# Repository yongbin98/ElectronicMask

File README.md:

# ElectronicMask
The code is for the assignment "Developing breathing-based vital signs detection models and control algorithms to improve sleep quality" <br>

# Sensors
`MCU` : STM32F765VI <br>
`Bluetooth` : E104-BT5005A <br>
`Pressure Sensor` : LPS22HHTR <br>
`Microphone` : SPH0645LM4H-1-8 <br>
`IMU Sensor` : LSM6DSMTR <br>
`PPG Sensor` : MAX86171 & SFH 7072 <br>
`EMG EOG EEG sensor` : ADS1299 <br>

# Developed ElectronicMask (Prototype)

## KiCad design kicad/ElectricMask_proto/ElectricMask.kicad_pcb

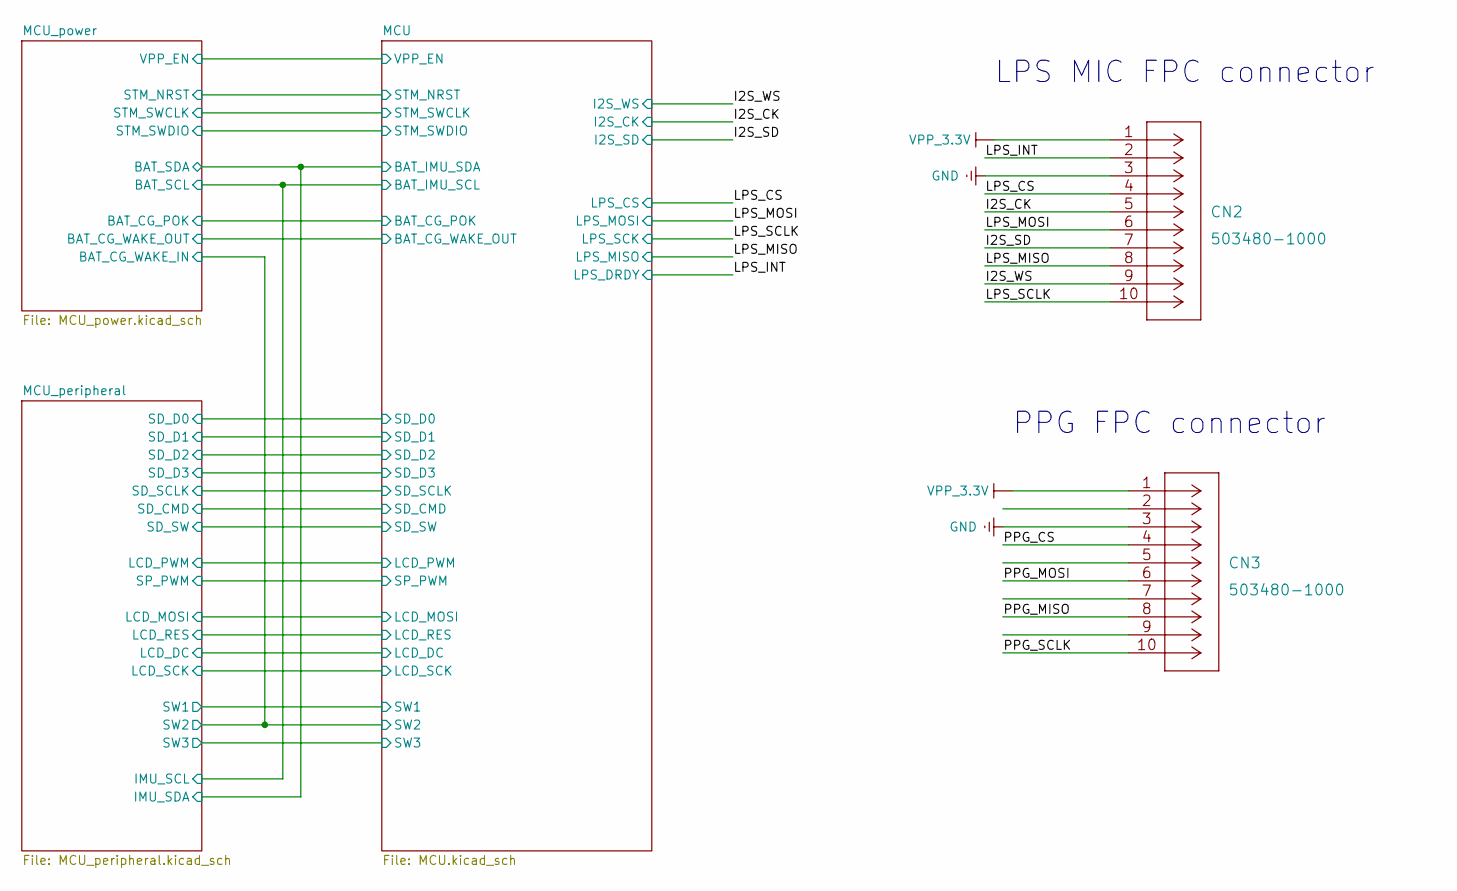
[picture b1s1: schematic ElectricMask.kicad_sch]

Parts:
CN2, CN3: 503480-1000

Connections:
/I2S_CK: CN2.5; also elsewhere on the board
/I2S_SD: CN2.7; also elsewhere on the board
/I2S_WS: CN2.9; also elsewhere on the board
/LPS_CS: CN2.4; also elsewhere on the board
/LPS_INT: CN2.2; also elsewhere on the board
/LPS_MISO: CN2.8; also elsewhere on the board
/LPS_MOSI: CN2.6; also elsewhere on the board
/LPS_SCLK: CN2.10; also elsewhere on the board

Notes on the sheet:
PPG FPC connector
LPS MIC FPC connector

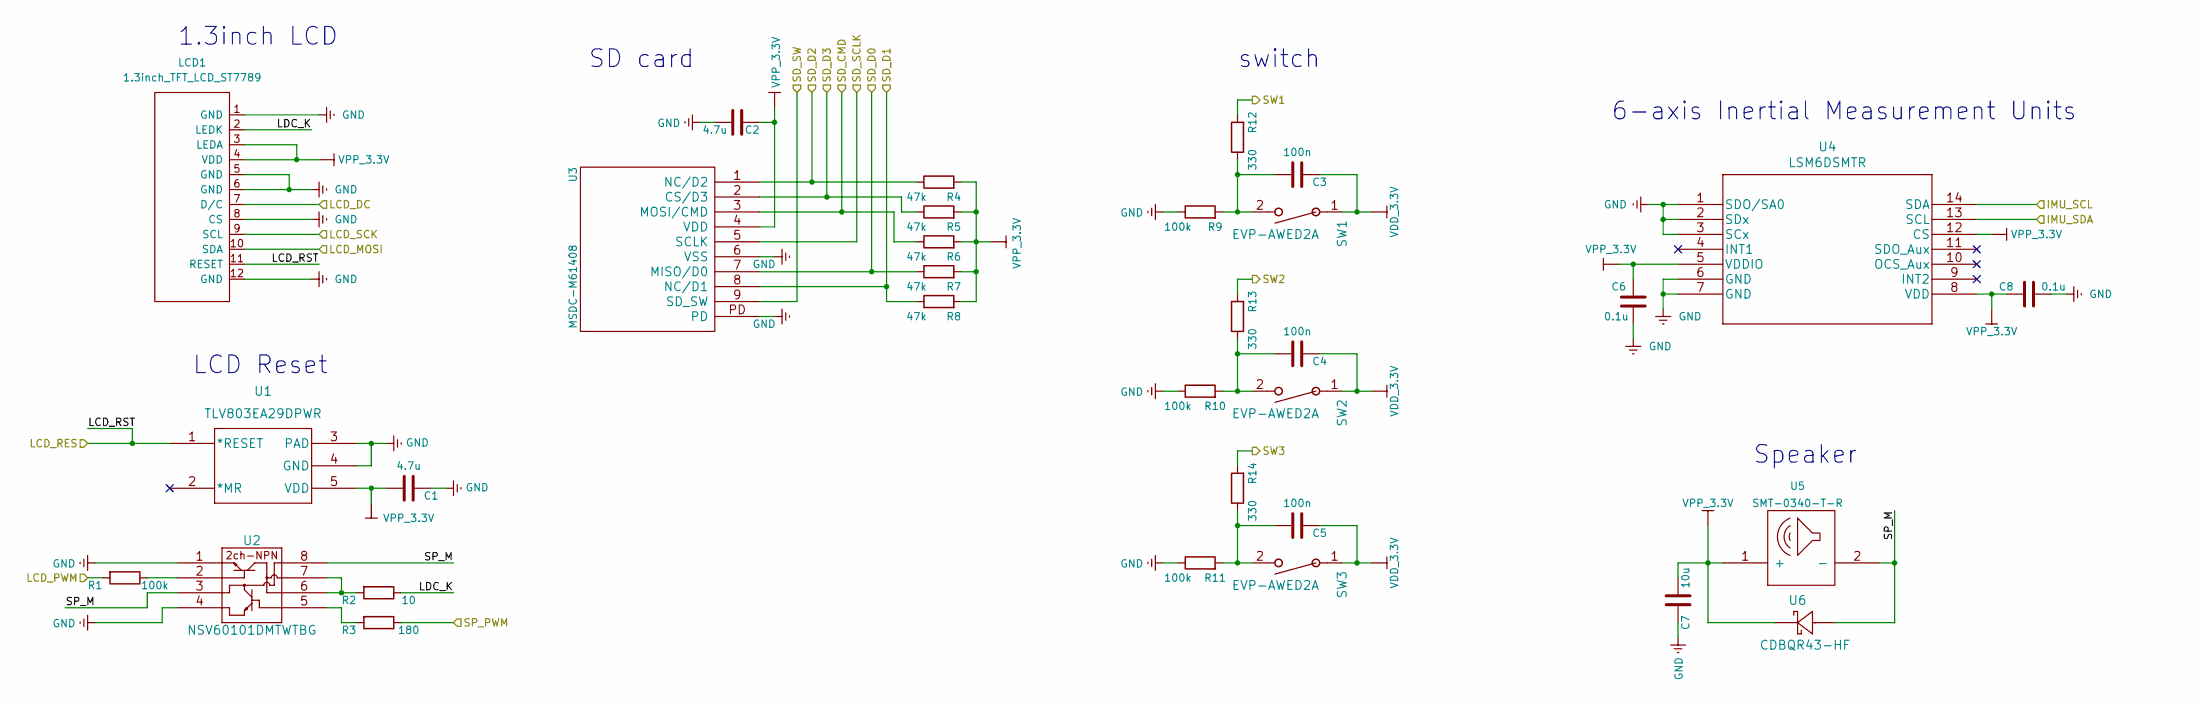
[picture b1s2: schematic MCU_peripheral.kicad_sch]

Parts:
C1, C2: 4.7u; UL_C_0402_1005Metric
C3, C4, C5: 100n; UL_C_0402_1005Metric
C6, C8: 0.1u; UL_C_0402_1005Metric
C7: 10u; UL_C_0402_1005Metric
LCD1: 1.3inch_TFT_LCD_ST7789
R1, R9, R10, R11: 100k; R_0402_1005Metric
R2: 10; R_0402_1005Metric
R3: 180; R_0402_1005Metric
R4, R5, R6, R7, R8: 47k; R_0402_1005Metric
R12, R13, R14: 330; R_0402_1005Metric
SW1, SW2, SW3: EVP-AWED2A
U1: TLV803EA29DPWR
U2: NSV60101DMTWTBG
U3: MSDC-M61408; MSDC-M61408(Micro_SD)
U4: LSM6DSMTR
U5: SMT-0340-T-R
U6: CDBQR43-HF

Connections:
/MCU/BAT_IMU_SCL: U4.14 (SDA); also elsewhere on the board
/MCU/BAT_IMU_SDA: U4.13 (SCL); also elsewhere on the board
/MCU/LCD_DC: LCD1.7 (D/C); also elsewhere on the board
/MCU/LCD_MOSI: LCD1.10 (SDA); also elsewhere on the board
/MCU/LCD_PWM: R1.2; also elsewhere on the board
/MCU/LCD_SCK: LCD1.9 (SCL); also elsewhere on the board
/MCU/SD_CMD: R6.1, U3.3 (MOSI/CMD); also elsewhere on the board
/MCU/SD_D0: R7.1, U3.7 (MISO/D0); also elsewhere on the board
/MCU/SD_D1: R8.1, U3.8 (NC/D1); also elsewhere on the board
/MCU/SD_D2: R4.1, U3.1 (NC/D2); also elsewhere on the board
/MCU/SD_D3: R5.1, U3.2 (CS/D3); also elsewhere on the board
/MCU/SD_SCLK: U3.5 (SCLK); also elsewhere on the board
/MCU/SD_SW: U3.9 (SD_SW); also elsewhere on the board
/MCU/SP_PWM: R3.1; also elsewhere on the board
/MCU/SW1: R12.2; also elsewhere on the board
/MCU/SW2: R13.2; also elsewhere on the board
/MCU/SW3: R14.2; also elsewhere on the board
/MCU_peripheral/LCD_RST: LCD1.11 (RESET), U1.1 (*RESET); also elsewhere on the board
/MCU_peripheral/LDC_K: LCD1.2 (LEDK), R2.1
/MCU_peripheral/SP_M: U2.3, U2.8, U5.2 (-), U6.2
unnamed: C3.2, R9.2, R12.1, SW1.2
unnamed: C4.2, R10.2, R13.1, SW2.2
unnamed: C5.2, R11.2, R14.1, SW3.2
unnamed: R1.1, U2.2
unnamed: R2.2, U2.6, U2.7
unnamed: R3.2, U2.5
VDD_3_3V: C3.1, C4.1, C5.1, SW1.1, SW2.1, SW3.1; also elsewhere on the board

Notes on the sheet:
Speaker
6-axis Inertial Measurement Units
LCD Reset
SD card
1.3inch LCD
switch

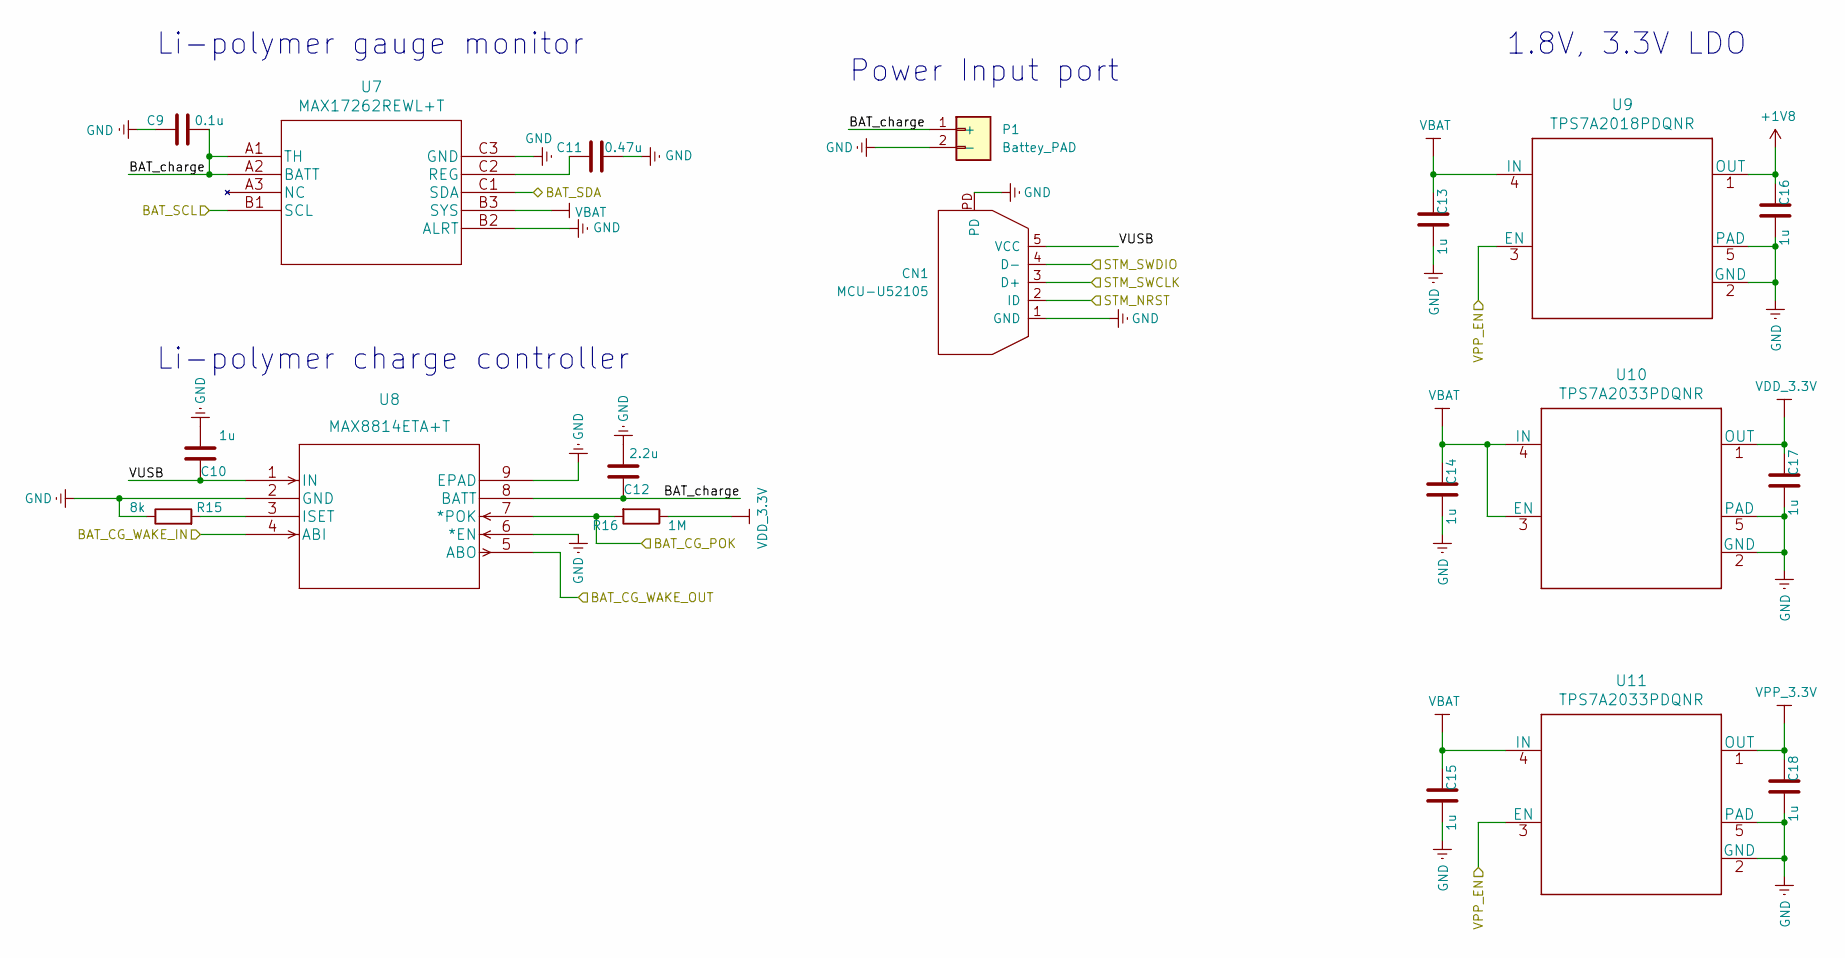
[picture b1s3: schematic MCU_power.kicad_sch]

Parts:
C9: 0.1u; UL_C_0402_1005Metric
C10, C13, C14, C15, C16, C17, C18: 1u; UL_C_0402_1005Metric
C11: 0.47u; UL_C_0402_1005Metric
C12: 2.2u; UL_C_0402_1005Metric
CN1: MCU-U52105
P1: Battey_PAD
R15: 8k; R_0402_1005Metric
R16: 1M; R_0402_1005Metric
U7: MAX17262REWL+T; MAX17262REWL&plus_T
U8: MAX8814ETA+T; MAX8814ETA&plus_T
U9: TPS7A2018PDQNR; X2SON-4PIN
U10, U11: TPS7A2033PDQNR; X2SON-4PIN

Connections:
+1V8: C16.2, U9.1 (OUT)
/MCU/BAT_CG_POK: R16.2, U8.7 (*POK); also elsewhere on the board
/MCU/BAT_CG_WAKE_OUT: U8.5 (ABO); also elsewhere on the board
/MCU/BAT_IMU_SCL: U7.B1 (SCL); also elsewhere on the board
/MCU/BAT_IMU_SDA: U7.C1 (SDA); also elsewhere on the board
/MCU/STM_NRST: CN1.2 (ID); also elsewhere on the board
/MCU/STM_SWCLK: CN1.3 (D+); also elsewhere on the board
/MCU/STM_SWDIO: CN1.4 (D-); also elsewhere on the board
/MCU/SW2: U8.4 (ABI); also elsewhere on the board
/MCU/VPP_EN: U9.3 (EN), U11.3 (EN); also elsewhere on the board
/MCU_power/BAT_charge: C9.2, C12.1, P1.1 (+), U7.A1 (TH), U7.A2 (BATT), U8.8 (BATT)
/MCU_power/VUSB: C10.1, CN1.5 (VCC), U8.1 (IN)
unnamed: C11.2, U7.C2 (REG)
unnamed: R15.2, U8.3 (ISET)
VBAT: C13.2, C14.2, C15.2, U7.B3 (SYS), U9.4 (IN), U10.3 (EN), U10.4 (IN), U11.4 (IN)
VDD_3_3V: C17.2, R16.1, U10.1 (OUT); also elsewhere on the board

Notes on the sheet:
Power Input port
Li-polymer gauge monitor
1.8V, 3.3V LDO
Li-polymer charge controller

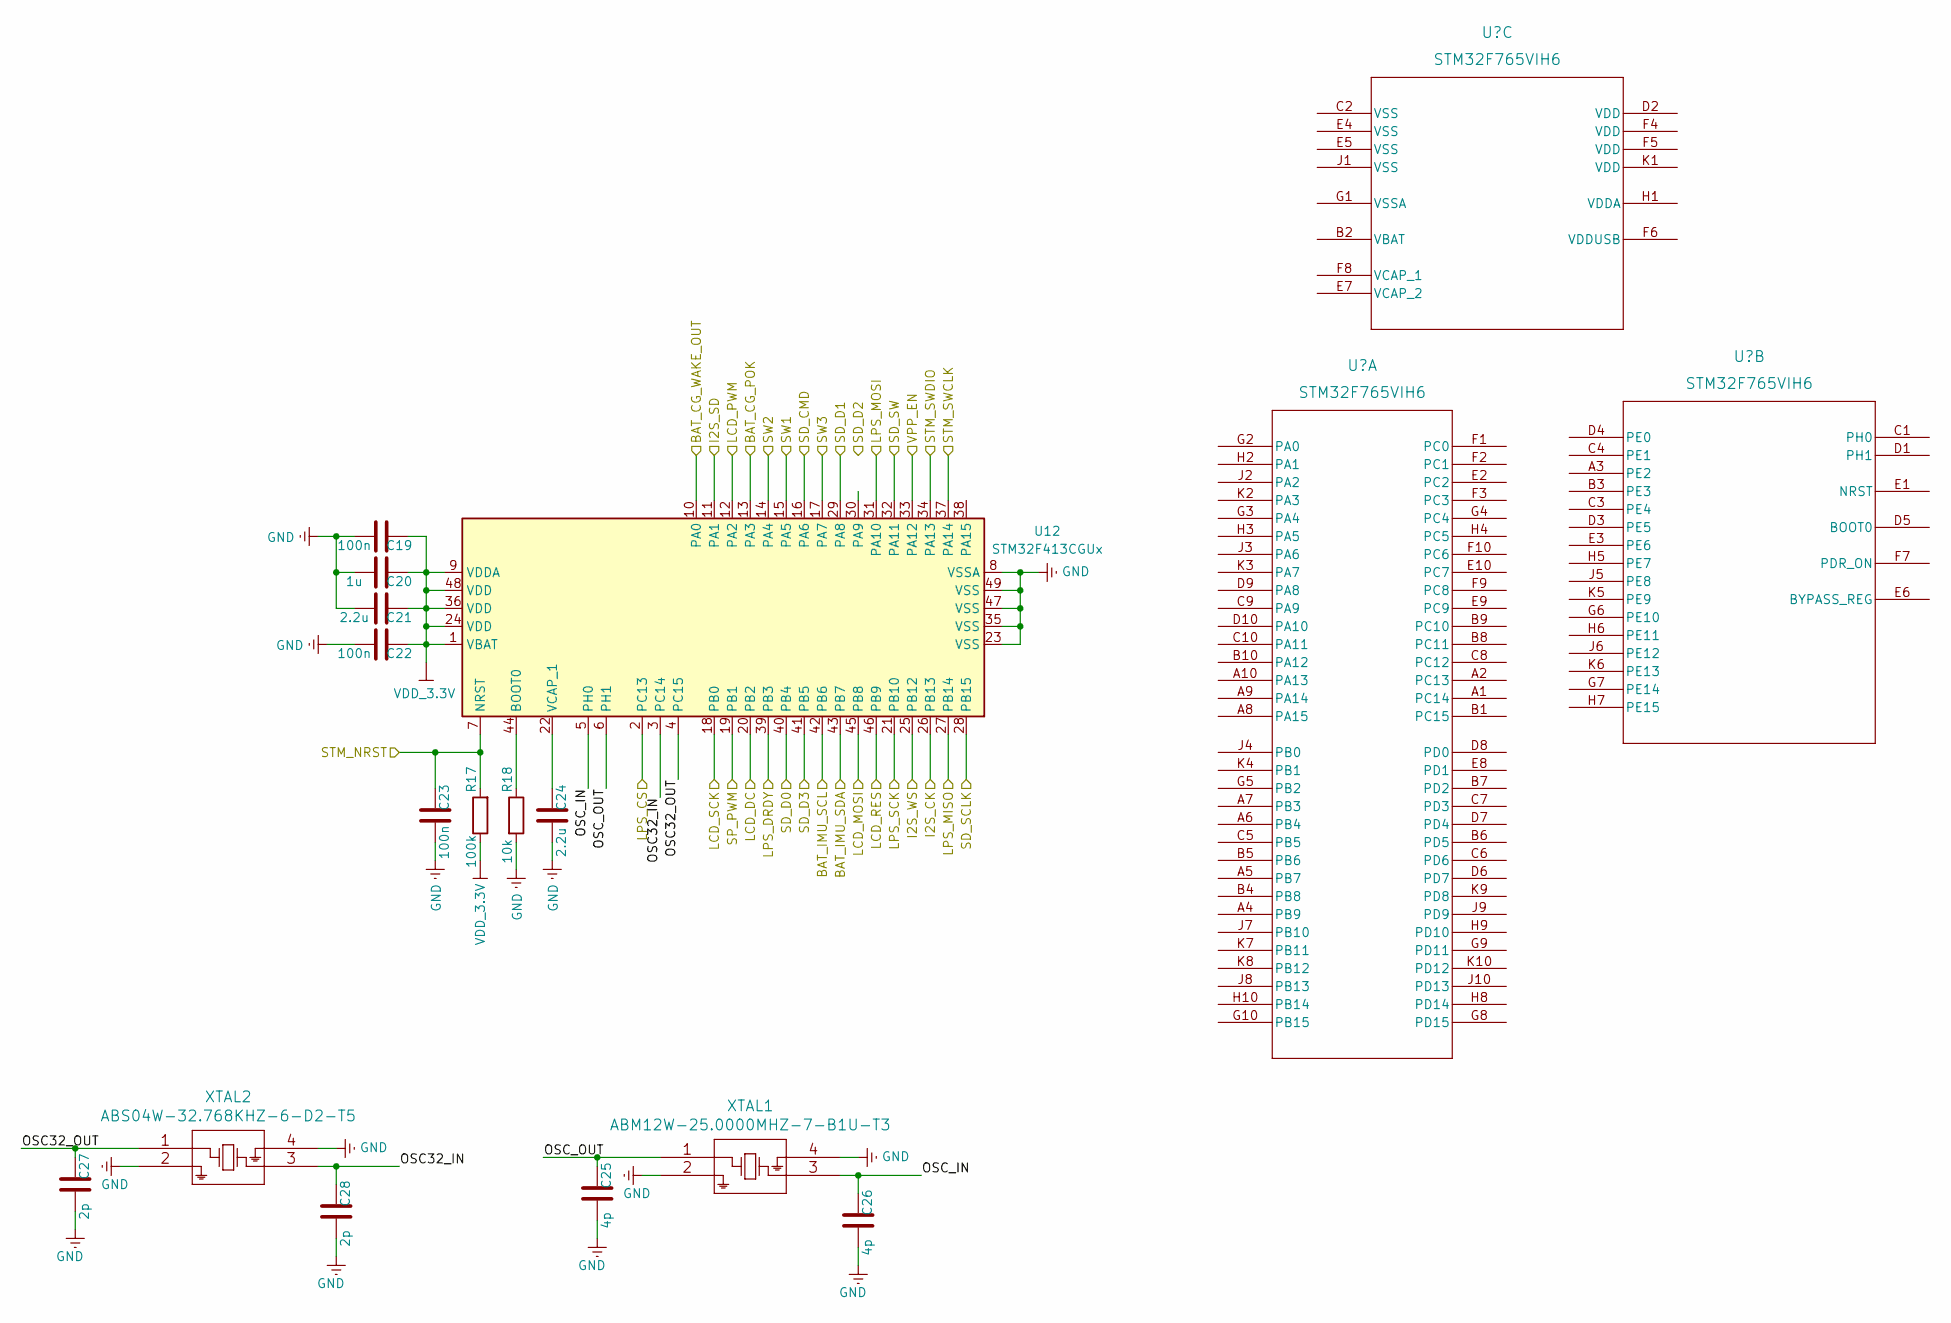
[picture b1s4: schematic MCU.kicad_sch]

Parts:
C19, C22, C23: 100n; UL_C_0402_1005Metric
C20: 1u; UL_C_0402_1005Metric
C21, C24: 2.2u; UL_C_0402_1005Metric
C25, C26: 4p; UL_C_0402_1005Metric
C27, C28: 2p; UL_C_0402_1005Metric
R17: 100k; R_0402_1005Metric
R18: 10k; R_0402_1005Metric
U12: STM32F413CGUx; QFN-48-1EP_7x7mm_P0.5mm_EP5.6x5.6mm
XTAL1: ABM12W-25.0000MHZ-7-B1U-T3; ABM12W
XTAL2: ABS04W-32.768KHZ-6-D2-T5; ABS04W

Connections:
/I2S_CK: U12.26 (PB13); also elsewhere on the board
/I2S_SD: U12.11 (PA1); also elsewhere on the board
/I2S_WS: U12.25 (PB12); also elsewhere on the board
/LPS_CS: U12.2 (PC13); also elsewhere on the board
/LPS_INT: U12.39 (PB3); also elsewhere on the board
/LPS_MISO: U12.27 (PB14); also elsewhere on the board
/LPS_MOSI: U12.31 (PA10); also elsewhere on the board
/LPS_SCLK: U12.21 (PB10); also elsewhere on the board
/MCU/BAT_CG_POK: U12.13 (PA3); also elsewhere on the board
/MCU/BAT_CG_WAKE_OUT: U12.10 (PA0); also elsewhere on the board
/MCU/BAT_IMU_SCL: U12.42 (PB6); also elsewhere on the board
/MCU/BAT_IMU_SDA: U12.43 (PB7); also elsewhere on the board
/MCU/LCD_DC: U12.20 (PB2); also elsewhere on the board
/MCU/LCD_MOSI: U12.45 (PB8); also elsewhere on the board
/MCU/LCD_PWM: U12.12 (PA2); also elsewhere on the board
/MCU/LCD_SCK: U12.18 (PB0); also elsewhere on the board
/MCU/OSC32_IN: C28.2, U12.3 (PC14), XTAL2.3
/MCU/OSC32_OUT: C27.2, U12.4 (PC15), XTAL2.1
/MCU/OSC_IN: C26.2, U12.5 (PH0), XTAL1.3
/MCU/OSC_OUT: C25.2, U12.6 (PH1), XTAL1.1
/MCU/SD_CMD: U12.16 (PA6); also elsewhere on the board
/MCU/SD_D0: U12.40 (PB4); also elsewhere on the board
/MCU/SD_D1: U12.29 (PA8); also elsewhere on the board
/MCU/SD_D2: U12.30 (PA9); also elsewhere on the board
/MCU/SD_D3: U12.41 (PB5); also elsewhere on the board
/MCU/SD_SCLK: U12.28 (PB15); also elsewhere on the board
/MCU/SD_SW: U12.32 (PA11); also elsewhere on the board
/MCU/SP_PWM: U12.19 (PB1); also elsewhere on the board
/MCU/STM_NRST: C23.2, R17.2, U12.7 (NRST); also elsewhere on the board
/MCU/STM_SWCLK: U12.37 (PA14); also elsewhere on the board
/MCU/STM_SWDIO: U12.34 (PA13); also elsewhere on the board
/MCU/SW1: U12.15 (PA5); also elsewhere on the board
/MCU/SW2: U12.14 (PA4); also elsewhere on the board
/MCU/SW3: U12.17 (PA7); also elsewhere on the board
/MCU/VPP_EN: U12.33 (PA12); also elsewhere on the board
/MCU_peripheral/LCD_RST: U12.46 (PB9); also elsewhere on the board
unnamed: C24.2, U12.22 (VCAP_1)
unnamed: R18.1, U12.44 (BOOT0)
VDD_3_3V: C19.2, C20.2, C21.2, C22.2, R17.1, U12.1 (VBAT), U12.9 (VDDA), U12.24 (VDD), U12.36 (VDD), U12.48 (VDD); also elsewhere on the board

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
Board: 2 copper layers, 67 parts (0 on the bottom side), 57 nets, no tracks yet.

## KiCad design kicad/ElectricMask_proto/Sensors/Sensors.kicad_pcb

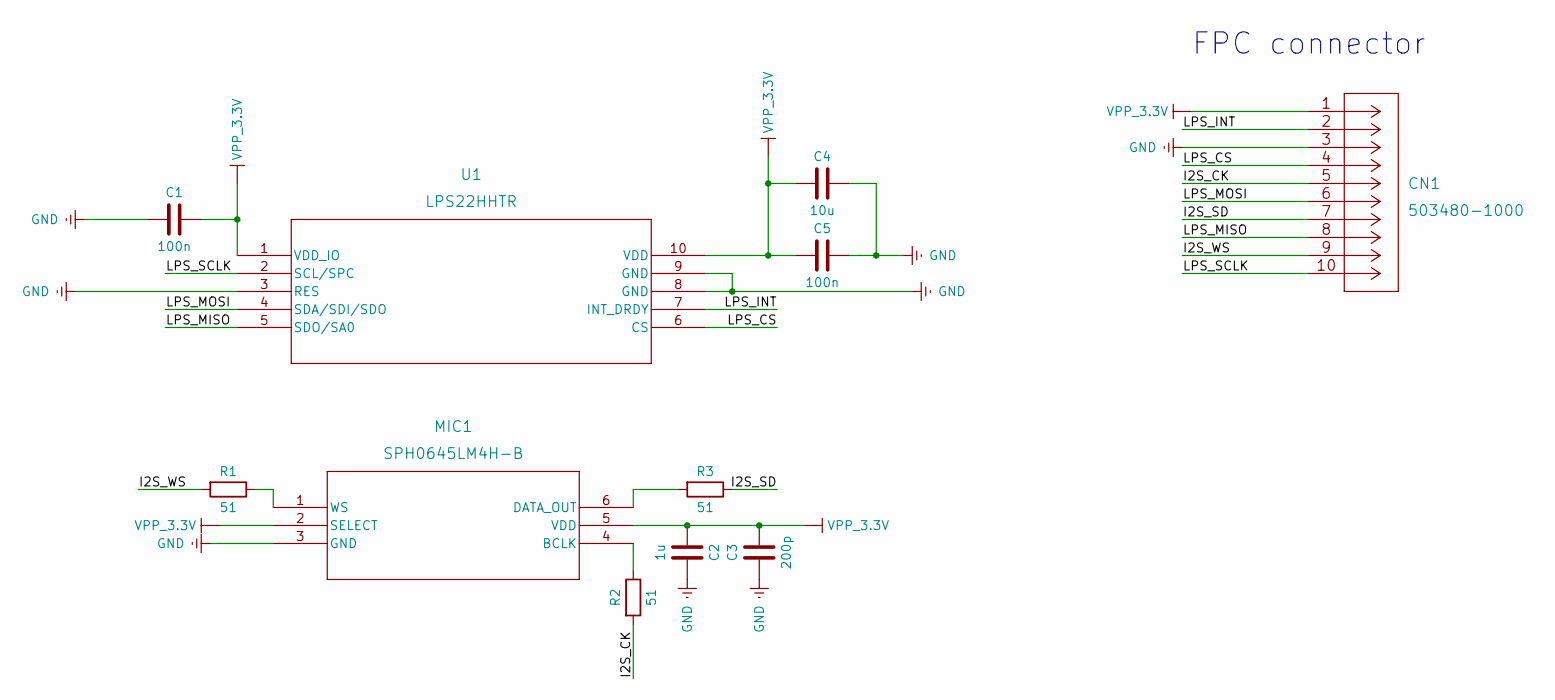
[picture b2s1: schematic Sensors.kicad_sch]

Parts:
C1, C5: 100n; UL_C_0402_1005Metric
C2: 1u; UL_C_0402_1005Metric
C3: 200p; UL_C_0402_1005Metric
C4: 10u; UL_C_0402_1005Metric
CN1: 503480-1000
MIC1: SPH0645LM4H-B; SPH0645LM4H-B_KNO
R1, R2, R3: 51; R_0402_1005Metric
U1: LPS22HHTR; HLGA-10L_2X2X0P73_STM

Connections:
/I2S_CK: CN1.5, R2.2
/I2S_SD: CN1.7, R3.1
/I2S_WS: CN1.9, R1.2
/LPS_CS: CN1.4, U1.6 (CS)
/LPS_INT: CN1.2, U1.7 (INT_DRDY)
/LPS_MISO: CN1.8, U1.5 (SDO/SA0)
/LPS_MOSI: CN1.6, U1.4 (SDA/SDI/SDO)
/LPS_SCLK: CN1.10, U1.2 (SCL/SPC)
unnamed: MIC1.1 (WS), R1.1
unnamed: MIC1.4 (BCLK), R2.1
unnamed: MIC1.6 (DATA_OUT), R3.2
U_GND: C1.1, C2.2, C3.1, C4.2, C5.2, CN1.3, CN1.11, CN1.12, MIC1.3 (GND), U1.3 (RES), U1.8 (GND), U1.9 (GND)
VDD: C1.2, C2.1, C3.2, C4.1, C5.1, CN1.1, MIC1.2 (SELECT), MIC1.5 (VDD), U1.1 (VDD_IO), U1.10 (VDD)

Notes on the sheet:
FPC connector

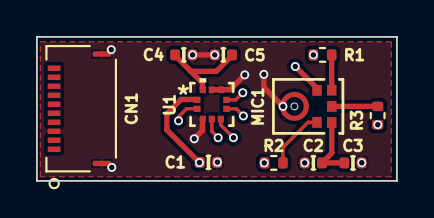
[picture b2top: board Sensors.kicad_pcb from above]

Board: 4 copper layers, 20.0 x 8.0 mm, 11 parts (0 on the bottom side), 13 nets.

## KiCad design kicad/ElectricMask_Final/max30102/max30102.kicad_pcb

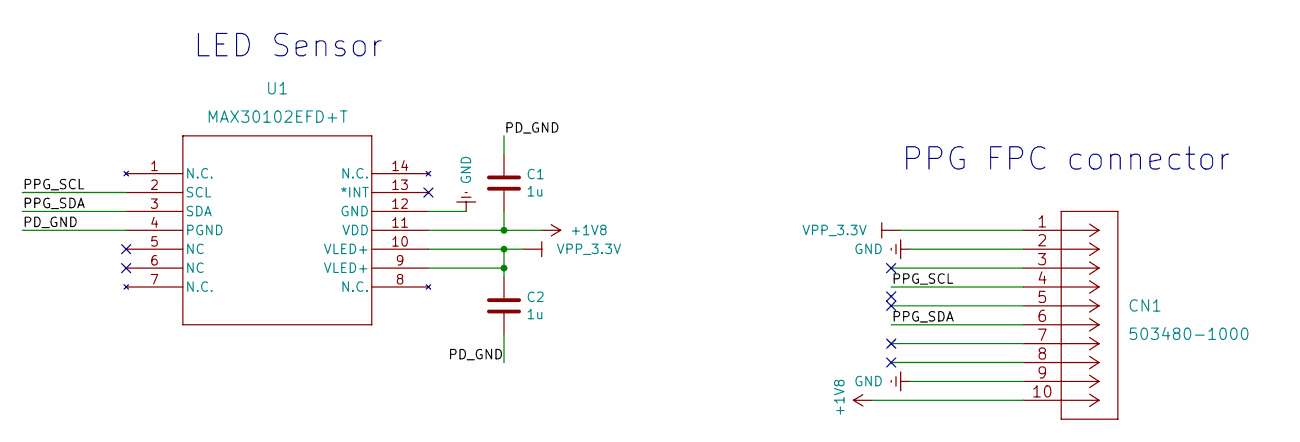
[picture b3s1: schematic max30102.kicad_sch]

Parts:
C1, C2: 1u; UL_C_0402_1005Metric
CN1: 503480-1000
U1: MAX30102EFD+T; MAX30102

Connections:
+1V8: C1.2, CN1.10, U1.11 (VDD)
/PD_GND: C1.1, C2.2, U1.4 (PGND)
/PPG_SCL: CN1.4, U1.2 (SCL)
/PPG_SDA: CN1.6, U1.3 (SDA)
U_GND: CN1.2, CN1.9, CN1.11, CN1.12, U1.12 (GND)
VPP_3_3V: C2.1, CN1.1, U1.9 (VLED+), U1.10 (VLED+)

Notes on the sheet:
LED Sensor
PPG FPC connector

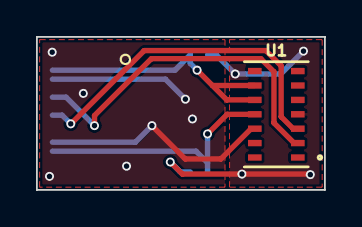
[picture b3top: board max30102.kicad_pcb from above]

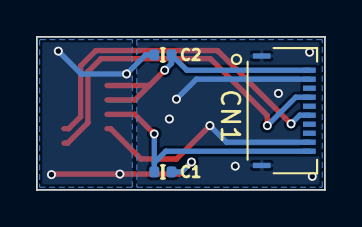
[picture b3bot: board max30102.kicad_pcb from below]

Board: 2 copper layers, 16.0 x 8.5 mm, 4 parts (3 on the bottom side), 6 nets.

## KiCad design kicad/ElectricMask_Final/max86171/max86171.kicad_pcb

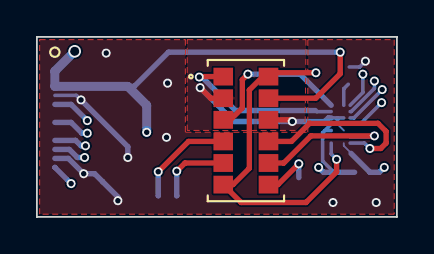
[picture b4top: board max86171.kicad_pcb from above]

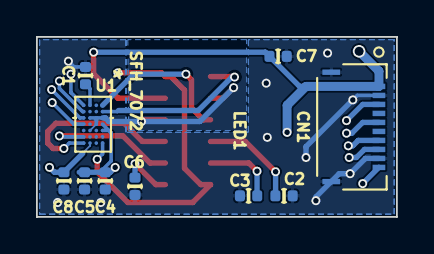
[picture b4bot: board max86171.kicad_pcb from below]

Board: 4 copper layers, 20.0 x 10.0 mm, 11 parts (10 on the bottom side), 13 nets.

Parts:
C1: 1u; UL_C_0402_1005Metric
C2, C3, C6, C7: 22u; UL_C_0402_1005Metric
C4, C8: 10u; UL_C_0402_1005Metric
C5: 0.1u; UL_C_0402_1005Metric
CN1: 503480-1000
LED1: SFH_7072; SFH 7072
U1: MAX86171ENI+; MAX86171ENI&plus_

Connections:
+1V8: C4.1, C5.1, CN1.10, U1.D3 (VDD_ANA), U1.D4 (VDD_DIG)
/LED3_DRV: LED1.9, U1.A1 (LED3_DRV)
/LED4_DRV: LED1.6, LED1.12, U1.D1 (LED4_DRV)
/LED9_DRV: LED1.8, U1.A2 (LED9_DRV)
/PD1_IN: LED1.3, U1.D7 (PD1_IN)
/PD2_IN: LED1.1, U1.D6 (PD2_IN)
/PPG_CS: CN1.3, U1.A7 (CSB/ADDR)
/PPG_MISO: CN1.7, U1.A5 (SDO)
/PPG_MOSI: CN1.5, U1.A6 (SDI/SDA)
/PPG_SCLK: CN1.8, U1.A4 (SCLK/SCL)
unnamed: C1.1, U1.B7 (VREF)
U_GND: C1.2, C2.2, C3.2, C4.2, C5.2, C6.2, C7.2, C8.2, CN1.2, CN1.9, CN1.11, CN1.12, LED1.2, LED1.10, U1.B3 (PGND), U1.B5 (TRIG), U1.C4 (I2C_SEL), U1.C5 (GND), U1.D5 (PD_GND)
VPP_3_3V: C2.1, C3.1, C6.1, C7.1, C8.1, CN1.1, LED1.4, LED1.5, LED1.7, LED1.11, U1.B1 (VLED)

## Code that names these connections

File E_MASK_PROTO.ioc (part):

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Mcu.Name=STM32F413C(G-H)Ux
Mcu.Package=UFQFPN48
Mcu.UserName=STM32F413CGUx
PA0.Mode=SYS_WakeUp0
PA0.Signal=SYS_WKUP1
PA1.GPIOParameters=GPIO_Speed,GPIO_PuPd,GPIO_Label
PA1.GPIO_Label=MIC_SD
PA1.GPIO_PuPd=GPIO_PULLUP
PA1.GPIO_Speed=GPIO_SPEED_FREQ_LOW
PA1.Mode=Half_Duplex_Master
PA1.Signal=I2S4_SD
PA10.GPIOParameters=GPIO_PuPd,GPIO_Label
PA10.GPIO_Label=LPS_MOSI
PA10.GPIO_PuPd=GPIO_PULLUP
PA10.Mode=Full_Duplex_Master
PA10.Signal=SPI2_MOSI
PA11.GPIOParameters=GPIO_PuPd,GPIO_Label
PA11.GPIO_Label=SD_SW
PA11.GPIO_PuPd=GPIO_PULLUP
PA11.Signal=GPIO_Input
PA12.GPIOParameters=GPIO_Label
PA12.GPIO_Label=VPP_EN
PA12.Signal=GPIO_Output
PA13.Mode=Serial_Wire
PA13.Signal=SYS_JTMS-SWDIO
PA14.Mode=Serial_Wire
PA14.Signal=SYS_JTCK-SWCLK
PA2.GPIOParameters=GPIO_PuPd,GPIO_Label
PA2.GPIO_Label=LCD_PWM
PA2.GPIO_PuPd=GPIO_PULLUP
PA2.Signal=S_TIM9_CH1
PA3.GPIOParameters=GPIO_Label
PA3.GPIO_Label=BLE_MOD
PA3.Signal=GPIO_Output
PA4.GPIOParameters=GPIO_Label
PA4.GPIO_Label=SW2
PA4.Signal=GPXTI4
PA5.GPIOParameters=GPIO_Label
PA5.GPIO_Label=SW1
PA5.Signal=GPXTI5
PA6.GPIOParameters=GPIO_PuPd,GPIO_Label
PA6.GPIO_Label=SD_CMD
PA6.GPIO_PuPd=GPIO_PULLUP
PA6.Mode=SD_4_bits_Wide_bus
PA6.Signal=SDIO_CMD
PA7.GPIOParameters=GPIO_Label
PA7.GPIO_Label=SW3
PA7.Signal=GPXTI7
PA8.GPIOParameters=GPIO_PuPd,GPIO_Label
PA8.GPIO_Label=SD_D1
PA8.GPIO_PuPd=GPIO_PULLUP
PA8.Mode=SD_4_bits_Wide_bus
PA8.Signal=SDIO_D1
PA9.GPIOParameters=GPIO_PuPd,GPIO_Label
PA9.GPIO_Label=SD_D2
PA9.GPIO_PuPd=GPIO_PULLUP
PA9.Mode=SD_4_bits_Wide_bus
PA9.Signal=SDIO_D2
PB0.GPIOParameters=GPIO_PuPd,GPIO_Label
PB0.GPIO_Label=LCD_SCK
PB0.GPIO_PuPd=GPIO_PULLUP
PB0.Mode=Simplex_Bidirectional_Master
PB0.Signal=SPI5_SCK
PB1.GPIOParameters=GPIO_Label
PB1.GPIO_Label=SP_PWM
PB1.Signal=S_TIM3_CH4
PB10.GPIOParameters=GPIO_PuPd,GPIO_Label
PB10.GPIO_Label=LPS_SCK
PB10.GPIO_PuPd=GPIO_PULLUP
PB10.Mode=Full_Duplex_Master
PB10.Signal=SPI2_SCK
PB12.GPIOParameters=GPIO_Speed,GPIO_PuPd,GPIO_Label
PB12.GPIO_Label=MIC_WS
PB12.GPIO_PuPd=GPIO_PULLUP
PB12.GPIO_Speed=GPIO_SPEED_FREQ_LOW
PB12.Mode=Half_Duplex_Master
PB12.Signal=I2S4_WS
PB13.GPIOParameters=GPIO_Speed,GPIO_PuPd,GPIO_Label
PB13.GPIO_Label=MIC_CK
PB13.GPIO_PuPd=GPIO_PULLUP
PB13.GPIO_Speed=GPIO_SPEED_FREQ_LOW
PB13.Mode=Half_Duplex_Master
PB13.Signal=I2S4_CK
PB14.GPIOParameters=GPIO_PuPd,GPIO_Label
PB14.GPIO_Label=LPS_MISO
PB14.GPIO_PuPd=GPIO_PULLUP
PB14.Mode=Full_Duplex_Master
PB14.Signal=SPI2_MISO
PB15.GPIOParameters=GPIO_PuPd,GPIO_Label
PB15.GPIO_Label=SD_CLK
PB15.GPIO_PuPd=GPIO_NOPULL
PB15.Mode=SD_4_bits_Wide_bus
PB15.Signal=SDIO_CK
PB2.GPIOParameters=GPIO_Label
PB2.GPIO_Label=LCD_DC
PB2.Signal=GPIO_Output
PB4.GPIOParameters=GPIO_PuPd,GPIO_Label
PB4.GPIO_Label=SD_D0
PB4.GPIO_PuPd=GPIO_PULLUP
PB4.Mode=SD_4_bits_Wide_bus
PB4.Signal=SDIO_D0
PB5.GPIOParameters=GPIO_PuPd,GPIO_Label
PB5.GPIO_Label=SD_D3
PB5.GPIO_PuPd=GPIO_PULLUP
PB5.Mode=SD_4_bits_Wide_bus
PB5.Signal=SDIO_D3
PB6.GPIOParameters=GPIO_Label,GPIO_Pu
PB6.GPIO_Label=BAT_IMU_SCL
PB6.GPIO_Pu=GPIO_PULLUP
PB6.Mode=I2C
PB6.Signal=I2C1_SCL
PB7.GPIOParameters=GPIO_Label,GPIO_Pu
PB7.GPIO_Label=BAT_IMU_SDA
PB7.GPIO_Pu=GPIO_PULLUP
PB7.Mode=I2C
PB7.Signal=I2C1_SDA
PB8.GPIOParameters=GPIO_PuPd,GPIO_Label
PB8.GPIO_Label=LCD_MOSI
PB8.GPIO_PuPd=GPIO_PULLUP
PB8.Mode=Simplex_Bidirectional_Master
PB8.Signal=SPI5_MOSI
PB9.GPIOParameters=GPIO_Label
PB9.GPIO_Label=LCD_RES
PB9.Signal=GPIO_Output
PC14-OSC32_IN.GPIOParameters=GPIO_PuPd,GPIO_Label
PC14-OSC32_IN.GPIO_Label=LPS_CS
PC14-OSC32_IN.GPIO_PuPd=GPIO_PULLUP
PC14-OSC32_IN.Signal=GPIO_Output
PC15-OSC32_OUT.GPIOParameters=GPIO_PuPd,GPIO_Label
PC15-OSC32_OUT.GPIO_Label=BAT_CG_POK
PC15-OSC32_OUT.GPIO_PuPd=GPIO_PULLUP
PC15-OSC32_OUT.Signal=GPIO_Input
PH0\ -\ OSC_IN.Mode=HSE-External-Oscillator
PH0\ -\ OSC_IN.Signal=RCC_OSC_IN
PH1\ -\ OSC_OUT.Mode=HSE-External-Oscillator
PH1\ -\ OSC_OUT.Signal=RCC_OSC_OUT
RCC.HSE_VALUE=25000000
RCC.SYSCLKFreq_VALUE=32000000
RCC.SYSCLKSource=RCC_SYSCLKSOURCE_PLLCLK
board=custom

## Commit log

2023-11-18 prototype

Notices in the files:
parts and their libraries:
Copyright 2021 Accelerated Designs. All rights reserved.
